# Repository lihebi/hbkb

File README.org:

#+TITLE: Hebi Keyboard

318x140mm

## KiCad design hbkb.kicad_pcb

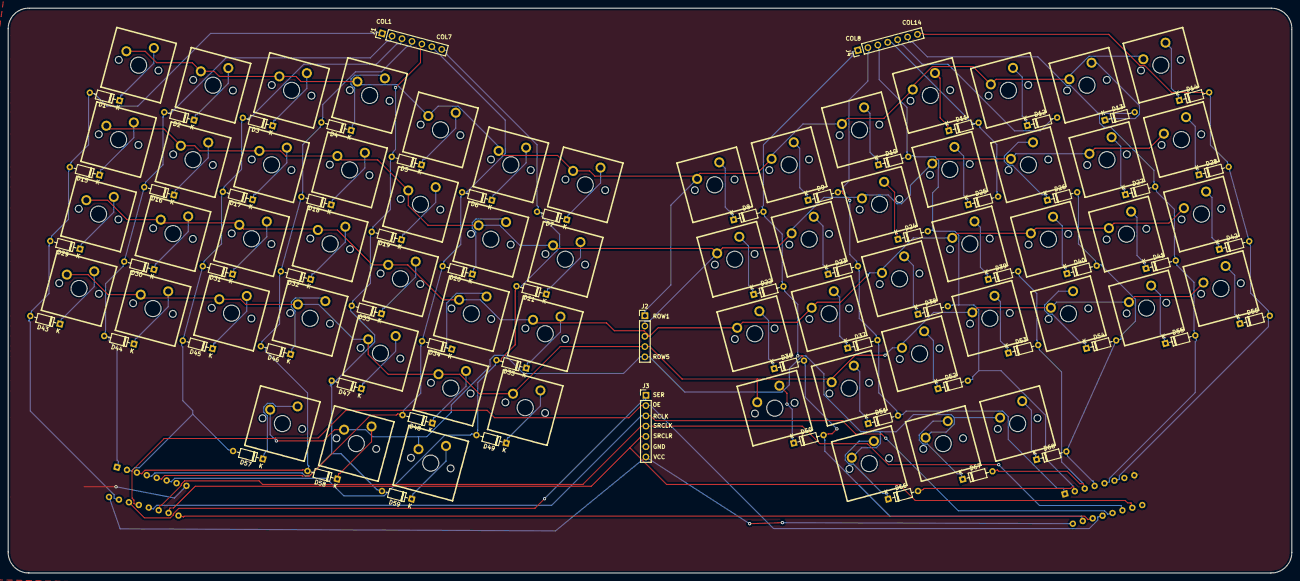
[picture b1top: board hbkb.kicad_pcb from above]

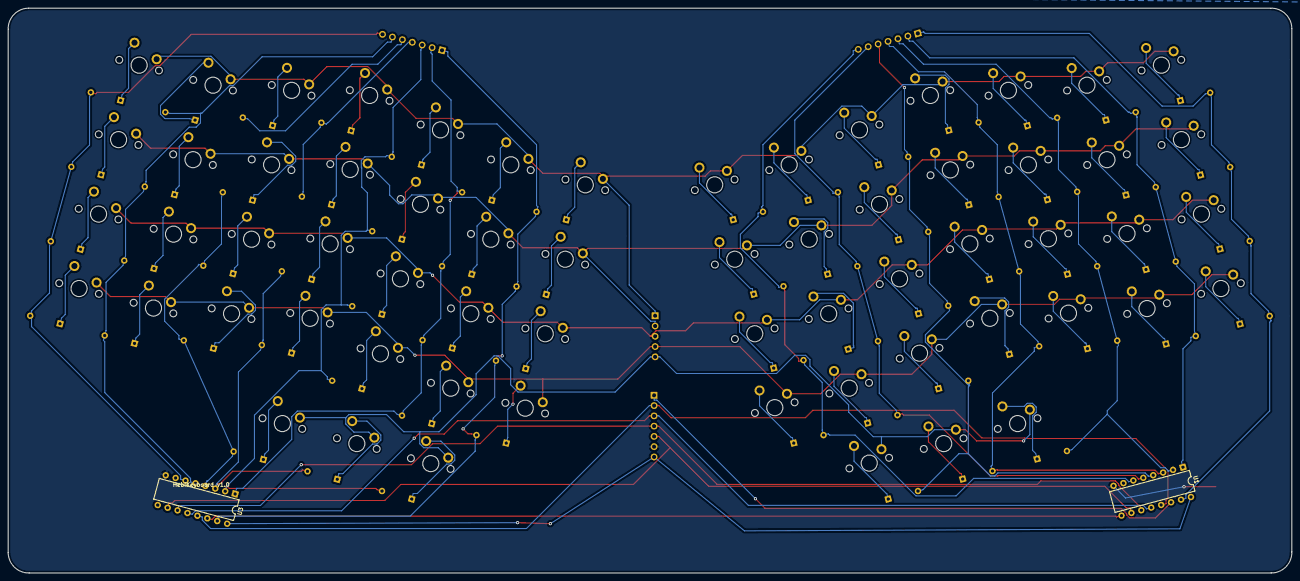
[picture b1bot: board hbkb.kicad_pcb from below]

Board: 2 copper layers, 317.5 x 139.7 mm, 130 parts (2 on the bottom side), 89 nets.

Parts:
D1, D2, D3, D4, D5, D6, D7, D8, D9, D10, D11, D12, D13, D14, D15, D16, D17, D18, D19, D20, D21, D22, D23, D24, D25, D26, D27, D28, D29, D30, D31, D32, D33, D34, D35, D36, D37, D38, D39, D40, D41, D42, D43, D44, D45, D46, D47, D48, D49, D50, D51, D52, D53, D54, D55, D56, D57, D58, D59, D66, D67, D68: 1N4148; D_DO-35_SOD27_P7.62mm_Horizontal
J1, J3, J4: Conn_01x07; PinHeader_1x07_P2.54mm_Vertical
J2: Conn_01x05; PinHeader_1x05_P2.54mm_Vertical
S1, S2, S3, S4, S5, S6, S7, S8, S9, S10, S11, S12, S13, S14, S15, S16, S17, S18, S19, S20, S21, S22, S23, S24, S25, S26, S27, S28, S29, S30, S31, S32, S33, S34, S35, S36, S37, S38, S39, S40, S41, S42, S43, S44, S45, S46, S47, S48, S49, S50, S51, S52, S53, S54, S55, S56, S57, S58, S59, S66, S67, S68: MX1A
U1, U3: 74HC595; DIP-16_W7.62mm

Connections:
+5V: J3.7, U1.16, U3.16
/COL1: D1.2, D15.2, D29.2, D43.2, J1.1, U1.15
/COL2: D2.2, D16.2, D30.2, D44.2, J1.2, U1.1
/COL3: D3.2, D17.2, D31.2, D45.2, D57.2, J1.3, U1.2
/COL4: D4.2, D18.2, D32.2, D46.2, D58.2, J1.4, U1.3
/COL5: D5.2, D19.2, D33.2, D47.2, D59.2, J1.5, U1.4
/COL6: D6.2, D20.2, D34.2, D48.2, J1.6, U1.5
/COL7: D7.2, D21.2, D35.2, D49.2, J1.7, U1.6
/COL8: D8.2, D22.2, D36.2, D50.2, J4.1, U3.15
/COL9: D9.2, D23.2, D37.2, D51.2, J4.2, U3.1
/COL10: D10.2, D24.2, D38.2, D52.2, D66.2, J4.3, U3.2
/COL11: D11.2, D25.2, D39.2, D53.2, D67.2, J4.4, U3.3
/COL12: D12.2, D26.2, D40.2, D54.2, D68.2, J4.5, U3.4
/COL13: D13.2, D27.2, D41.2, D55.2, J4.6, U3.5
/COL14: D14.2, D28.2, D42.2, D56.2, J4.7, U3.6
/KeyscanMatrix/ROW1: J2.1, S1.1, S2.1, S3.1, S4.1, S5.1, S6.1, S7.1, S8.1, S9.1, S10.1, S11.1, S12.1, S13.1, S14.1
/KeyscanMatrix/ROW2: J2.2, S15.1, S16.1, S17.1, S18.1, S19.1, S20.1, S21.1, S22.1, S23.1, S24.1, S25.1, S26.1, S27.1, S28.1
/KeyscanMatrix/ROW3: J2.3, S29.1, S30.1, S31.1, S32.1, S33.1, S34.1, S35.1, S36.1, S37.1, S38.1, S39.1, S40.1, S41.1, S42.1
/KeyscanMatrix/ROW4: J2.4, S43.1, S44.1, S45.1, S46.1, S47.1, S48.1, S49.1, S50.1, S51.1, S52.1, S53.1, S54.1, S55.1, S56.1
/KeyscanMatrix/ROW5: J2.5, S57.1, S58.1, S59.1, S66.1, S67.1, S68.1
/OE: J3.2, U1.13, U3.13
/RCLK: J3.3, U1.12, U3.12
/SER: J3.1, U1.14
/SRCLK: J3.4, U1.11, U3.11
/SRCLR: J3.5, U1.10, U3.10
GND: J3.6, U1.8, U3.8
unnamed: D1.1, S1.2
unnamed: D2.1, S2.2
unnamed: D3.1, S3.2
unnamed: D4.1, S4.2
unnamed: D5.1, S5.2
unnamed: D6.1, S6.2
unnamed: D7.1, S7.2
unnamed: D8.1, S8.2
unnamed: D9.1, S9.2
unnamed: D10.1, S10.2
unnamed: D11.1, S11.2
unnamed: D12.1, S12.2
unnamed: D13.1, S13.2
unnamed: D14.1, S14.2
unnamed: D15.1, S15.2
unnamed: D16.1, S16.2
unnamed: D17.1, S17.2
unnamed: D18.1, S18.2
unnamed: D19.1, S19.2
unnamed: D20.1, S20.2
unnamed: D21.1, S21.2
unnamed: D22.1, S22.2
unnamed: D23.1, S23.2
unnamed: D24.1, S24.2
unnamed: D25.1, S25.2
unnamed: D26.1, S26.2
unnamed: D27.1, S27.2
unnamed: D28.1, S28.2
unnamed: D29.1, S29.2
unnamed: D30.1, S30.2
unnamed: D31.1, S31.2
unnamed: D32.1, S32.2
unnamed: D33.1, S33.2
unnamed: D34.1, S34.2
unnamed: D35.1, S35.2
unnamed: D36.1, S36.2
unnamed: D37.1, S37.2
unnamed: D38.1, S38.2
unnamed: D39.1, S39.2
unnamed: D40.1, S40.2
unnamed: D41.1, S41.2
unnamed: D42.1, S42.2
unnamed: D43.1, S43.2
unnamed: D44.1, S44.2
unnamed: D45.1, S45.2
unnamed: D46.1, S46.2
unnamed: D47.1, S47.2
unnamed: D48.1, S48.2
unnamed: D49.1, S49.2
unnamed: D50.1, S50.2
unnamed: D51.1, S51.2
unnamed: D52.1, S52.2
unnamed: D53.1, S53.2
unnamed: D54.1, S54.2
unnamed: D55.1, S55.2
unnamed: D56.1, S56.2
unnamed: D57.1, S57.2
unnamed: D58.1, S58.2
unnamed: D59.1, S59.2
unnamed: D66.1, S66.2
unnamed: D67.1, S67.2
unnamed: D68.1, S68.2
unnamed: U1.9, U3.14

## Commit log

2019-03-27 init
2019-03-28 add shift register
2019-03-28 finish matrix routing, moving from 4 rows to 5 rows
2019-03-28 finish entire board
2019-03-28 entire copper fill
2019-03-30 adjust bottom row position
